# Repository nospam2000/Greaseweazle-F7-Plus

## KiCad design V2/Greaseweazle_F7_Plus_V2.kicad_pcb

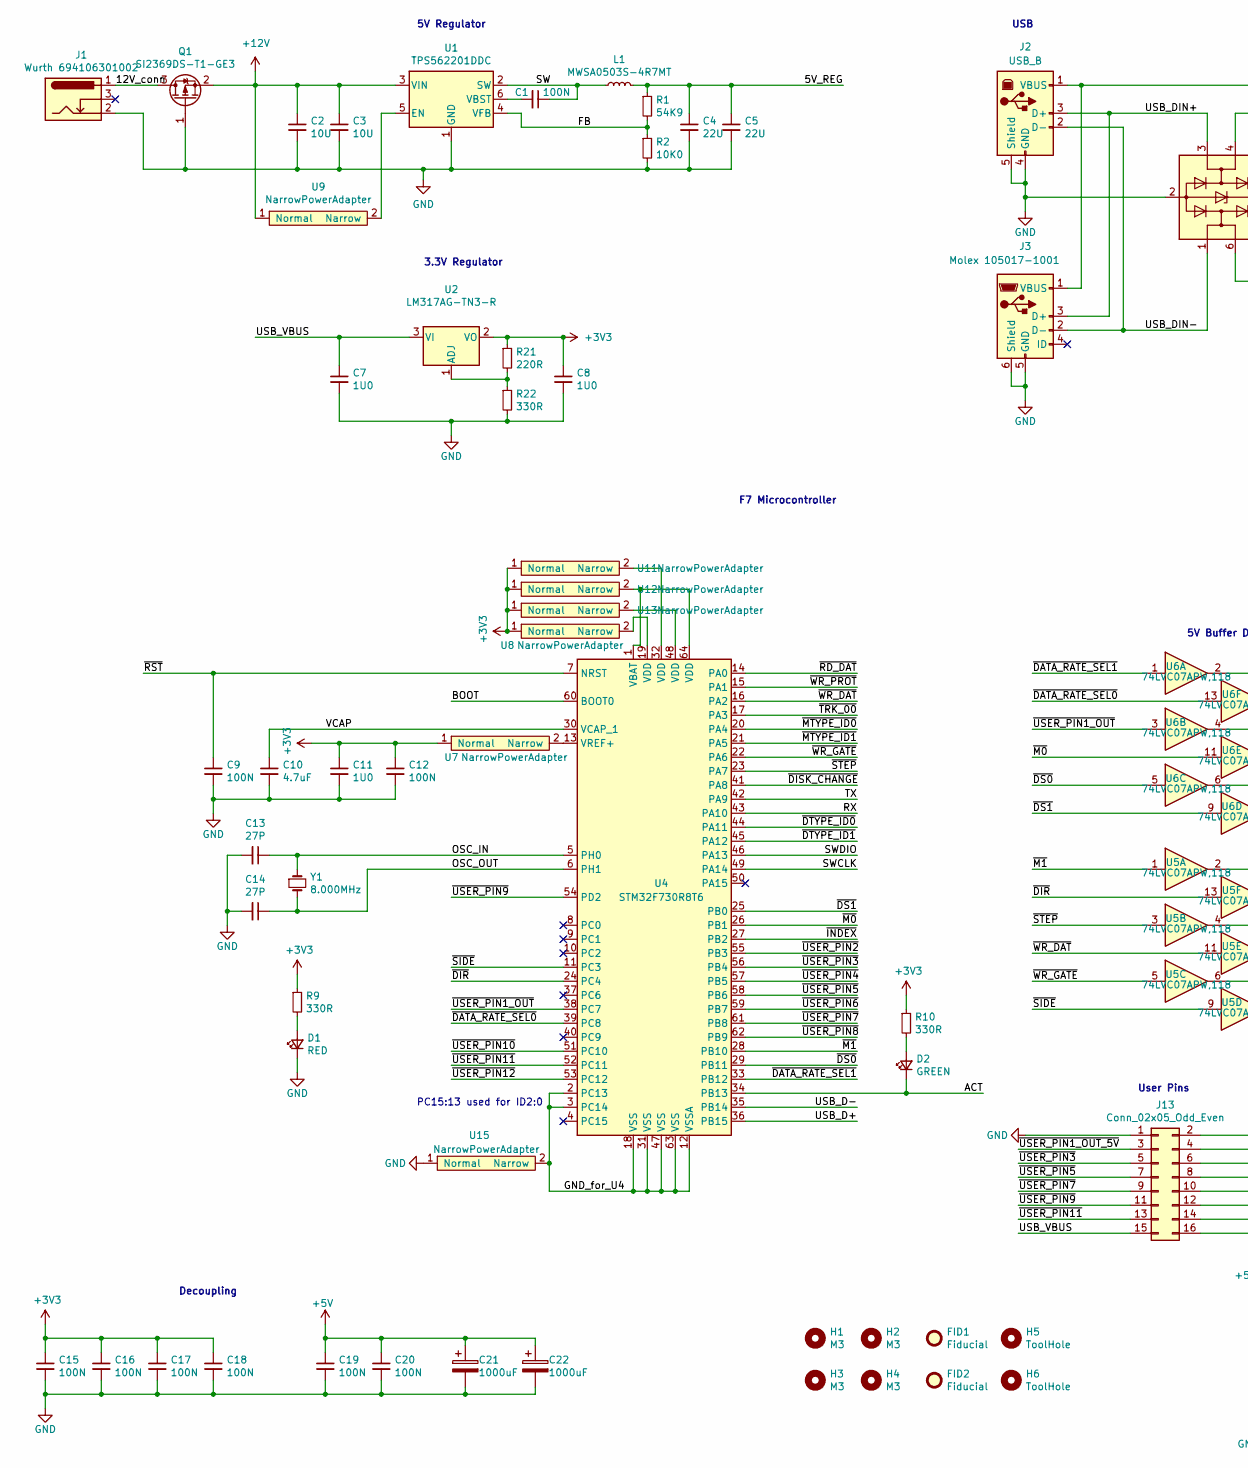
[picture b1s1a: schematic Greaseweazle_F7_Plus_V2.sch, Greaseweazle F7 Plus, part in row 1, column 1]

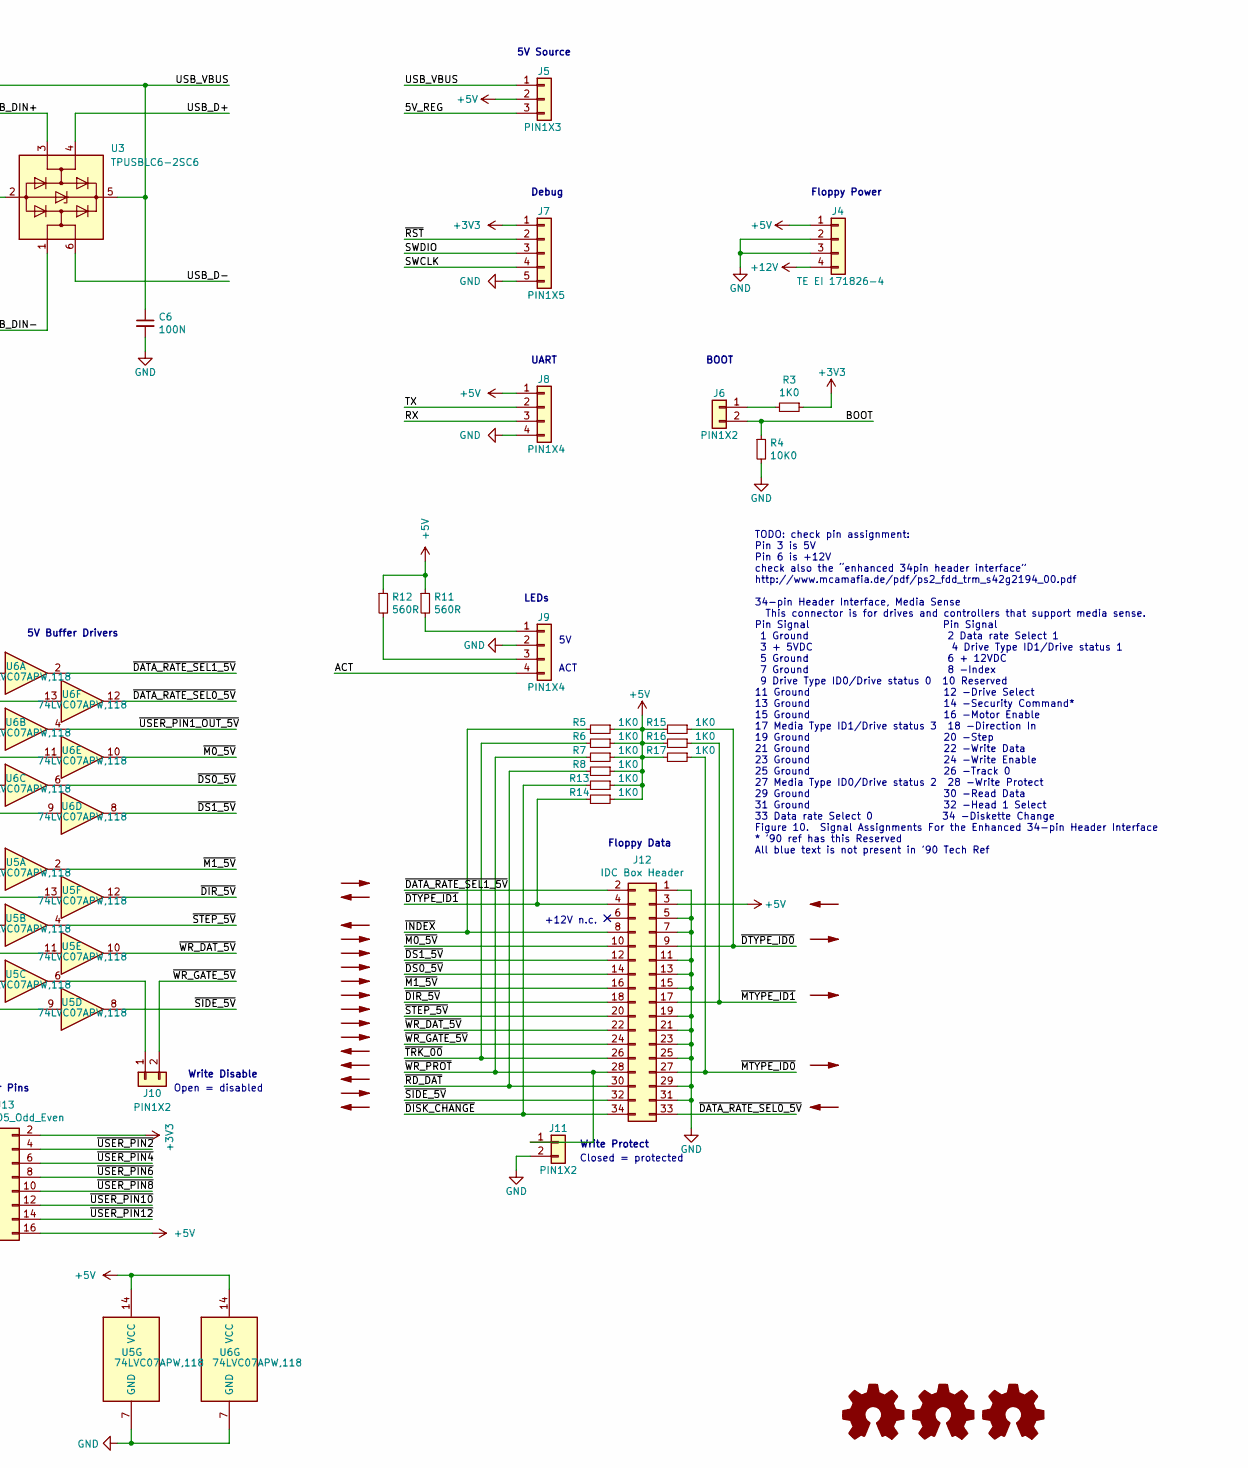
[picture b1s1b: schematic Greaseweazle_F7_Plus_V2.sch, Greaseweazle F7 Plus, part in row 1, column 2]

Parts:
C1, C6, C9, C12, C15, C16, C17, C18, C19, C20: 100N; C_0402_1005Metric; MFR.Part CL05B104KO5NNNC; LCSC C1525
C2, C3: 10U; C_0805_2012Metric; MFR.Part CL21A106KAYNNNE; LCSC C15850
C4, C5: 22U; C_0805_2012Metric; MFR.Part CL21A226MAQNNNE; LCSC C45783
C7, C8, C11: 1U0; C_0402_1005Metric; MFR.Part CL05A105KA5NQNC; LCSC C52923
C10: 4.7uF; C_0805_2012Metric; MFR.Part CL21A475KAQNNNE; LCSC C1779
C13, C14: 27P; C_0402_1005Metric; MFR.Part 0402CG270J500NTN; LCSC C1557
C21, C22: 1000uF; CP_Radial_D10.0mm_P5.00mm
D1: RED; LED_0603_1608Metric; MFR.Part KT-0603R; LCSC C2286
D2: GREEN; LED_0603_1608Metric; MFR.Part 19-217/GHC-YR1S2/3T; LCSC C72043
FID1, FID2: Fiducial; Fiducial_1mm_Mask2mm
H1, H2, H3, H4: M3; MountingHole_3mm
H5, H6: ToolHole; ToolingHole_1.152mm
J1: Wurth 694106301002; BarrelJack_Horizontal
J2: USB_B; USB_B_OST_USB-B1HSxx_Horizontal
J3: Molex 105017-1001; USB_Micro-B_Molex-105017-0001
J4: TE EI 171826-4; TE_171826-4_1x4_P2.50mm_Horizontal
J5: PIN1X3; PinHeader_1x03_P2.54mm_Vertical
J6, J10, J11: PIN1X2; PinHeader_1x02_P2.54mm_Vertical
J7: PIN1X5; PinHeader_1x05_P2.54mm_Vertical
J8, J9: PIN1X4; PinHeader_1x04_P2.54mm_Vertical
J12: IDC Box Header; IDC-Header_2x17_P2.54mm_Vertical
J13: Conn_02x05_Odd_Even; PinHeader_2x08_P2.54mm_Vertical
L1: MWSA0503S-4R7MT; L_5.4x5.2_H2.8; MFR.Part MWSA0503S-4R7MT; LCSC C408410
LOGO1: OSHW Logo; OSHW-Logo2_7.3x6mm_SilkScreen
LOGO2: GW Logo; Greaseweazle_Logo_small
LOGO3: GW Logo; Symbol_Barrel_Polarity
Q1: SI2369DS-T1-GE3; SOT-23; MFR.Part SI2369DS-T1-GE3; LCSC C141546
R1: 54K9; R_0603_1608Metric; MFR.Part 0603WAF5492T5E; LCSC C23077
R2, R4: 10K0; R_0603_1608Metric; MFR.Part 0603WAF1002T5E; LCSC C25804
R3, R5, R6, R7, R8, R13, R14, R15, R16, R17: 1K0; R_0805_2012Metric; MFR.Part 0805W8F1001T5E; LCSC C17513
R9, R10, R22: 330R; R_0805_2012Metric; MFR.Part 0805W8F3300T5E; LCSC C17630
R11, R12: 560R; R_0805_2012Metric; MFR.Part 0805W8F5600T5E; LCSC C28636
R21: 220R; R_0805_2012Metric; MFR.Part 0805W8F2200T5E; LCSC C17557
U1: TPS562201DDC; SOT-23-6; MFR.Part TPS562201DDCR; LCSC C90061
U2: LM317AG-TN3-R; TO-252-2; MFR.Part LM317AG-TN3-R; LCSC C75510
U3: TPUSBLC6-2SC6; SOT-23-6; MFR.Part TPUSBLC6-2SC6; LCSC C558442
U4: STM32F730R8T6; LQFP-64_10x10mm_P0.5mm; MFR.Part STM32F730R8T6; LCSC C478453
U5, U6: 74LVC07APW,118; TSSOP-14_4.4x5mm_P0.65mm; MFR.Part 74LVC07APW,118; LCSC C6051
U7, U8, U9, U11, U12, U13: NarrowPowerAdapter; NarrowPowerAdapter_0.60_to_0.25
U15: NarrowPowerAdapter; NarrowPowerAdapter_0.60_to_0.25_thick
Y1: 8.000MHz; Crystal_SMD_5032-2Pin_5.0x3.2mm; MFR.Part X50328MSB2GI; LCSC C115962

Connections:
+3V3: C8.1, C11.1, C12.1, C15.1, C16.1, C17.1, C18.1, J7.1, J13.2, R3.1, R9.1, R10.1, R21.1, U2.2 (VO), U7.1 (Normal), U8.1 (Normal), U11.1 (Normal), U12.1 (Normal), U13.1 (Normal)
+5V: C19.1, C20.1, C21.1, C22.1, J4.1, J5.2, J8.1, J12.3, J13.16, R5.1, R6.1, R7.1, R8.1, R11.1, R12.1, R13.1, R14.1, R15.2, R16.2, R17.2, U5.14 (VCC), U6.14 (VCC)
+12V: C2.1, C3.1, J4.4, Q1.2 (S), U1.3 (VIN), U9.1 (Normal)
/5V_REG: C4.1, C5.1, J5.3, L1.2, R1.1
/12V_conn: J1.1, Q1.3 (D)
/ACT: D2.1 (K), J9.4, U4.34 (PB13)
/BOOT: J6.2, R4.1, U4.60 (BOOT0)
/FB: R1.2, R2.1, U1.4 (VFB)
/GND_for_U4: U4.2 (PC13), U4.3 (PC14), U4.12 (VSSA), U4.18 (VSS), U4.31 (VSS), U4.47 (VSS), U4.63 (VSS), U15.2 (Narrow)
/OSC_IN: C13.1, U4.5 (PH0), Y1.1
/OSC_OUT: C14.1, U4.6 (PH1), Y1.2
/RX: J8.3, U4.43 (PA10)
/SW: C1.1, L1.1, U1.2 (SW)
/SWCLK: J7.4, U4.49 (PA14)
/SWDIO: J7.3, U4.46 (PA13)
/TX: J8.2, U4.42 (PA9)
/USB_D+: U3.4 (I/O2), U4.36 (PB15)
/USB_D-: U3.6 (I/O1), U4.35 (PB14)
/USB_DIN+: J2.3 (D+), J3.3 (D+), U3.3 (I/O2)
/USB_DIN-: J2.2 (D-), J3.2 (D-), U3.1 (I/O1)
/USB_VBUS: C6.1, C7.1, J2.1 (VBUS), J3.1 (VBUS), J5.1, J13.15, U2.3 (VI), U3.5 (VBUS)
/VCAP: C10.1, U4.30 (VCAP_1)
/~DATA_RATE_SEL0_5V~: J12.33, U6.12
/~DATA_RATE_SEL0~: U4.39 (PC8), U6.13
/~DATA_RATE_SEL1_5V~: J12.2, U6.2
/~DATA_RATE_SEL1~: U4.33 (PB12), U6.1
/~DIR_5V~: J12.18, U5.12
/~DIR~: U4.24 (PC4), U5.13
/~DISK_CHANGE~: J12.34, R13.2, U4.41 (PA8)
/~DS0_5V~: J12.14, U6.6
/~DS0~: U4.29 (PB11), U6.5
/~DS1_5V~: J12.12, U6.8
/~DS1~: U4.25 (PB0), U6.9
/~DTYPE_ID0~: J12.9, R15.1, U4.44 (PA11)
/~DTYPE_ID1~: J12.4, R14.2, U4.45 (PA12)
/~INDEX~: J12.8, R5.2, U4.27 (PB2)
/~M0_5V~: J12.10, U6.10
/~M0~: U4.26 (PB1), U6.11
/~M1_5V~: J12.16, U5.2
/~M1~: U4.28 (PB10), U5.1
/~MTYPE_ID0~: J12.27, R17.1, U4.20 (PA4)
/~MTYPE_ID1~: J12.17, R16.1, U4.21 (PA5)
/~RD_DAT~: J12.30, R8.2, U4.14 (PA0)
/~RST~: C9.1, J7.2, U4.7 (NRST)
/~SIDE_5V~: J12.32, U5.8
/~SIDE~: U4.11 (PC3), U5.9
/~STEP_5V~: J12.20, U5.4
/~STEP~: U4.23 (PA7), U5.3
/~TRK_00~: J12.26, R6.2, U4.17 (PA3)
/~USER_PIN1_OUT_5V~: J13.3, U6.4
/~USER_PIN1_OUT~: U4.38 (PC7), U6.3
/~USER_PIN2~: J13.4, U4.55 (PB3)
/~USER_PIN3~: J13.5, U4.56 (PB4)
/~USER_PIN4~: J13.6, U4.57 (PB5)
/~USER_PIN5~: J13.7, U4.58 (PB6)
/~USER_PIN6~: J13.8, U4.59 (PB7)
/~USER_PIN7~: J13.9, U4.61 (PB8)
/~USER_PIN8~: J13.10, U4.62 (PB9)
/~USER_PIN9~: J13.11, U4.54 (PD2)
/~USER_PIN10~: J13.12, U4.51 (PC10)
/~USER_PIN11~: J13.13, U4.52 (PC11)
/~USER_PIN12~: J13.14, U4.53 (PC12)
/~WR_DAT_5V~: J12.22, U5.10
/~WR_DAT~: U4.16 (PA2), U5.11
/~WR_GATE_5V~: J10.2, J12.24
/~WR_GATE~: U4.22 (PA6), U5.5
/~WR_PROT~: J11.1, J12.28, R7.2, U4.15 (PA1)
GND: C2.2, C3.2, C4.2, C5.2, C6.2, C7.2, C8.2, C9.2, C10.2, C11.2, C12.2, C13.2, C14.2, C15.2, C16.2, C17.2, C18.2, C19.2, C20.2, C21.2, C22.2, D1.1 (K), J1.2, J2.4 (GND), J2.5 (Shield), J3.5 (GND), J3.6 (Shield), J4.2, J4.3, J7.5, J8.4, J9.2, J11.2, J12.1, J12.5, J12.7, J12.11, J12.13, J12.15, J12.19, J12.21, J12.23, J12.25, J12.29, J12.31, J13.1, Q1.1 (G), R2.2, R4.2, R22.2, U1.1 (GND), U3.2 (GND), U5.7 (GND), U6.7 (GND), U15.1 (Normal)
unnamed: C1.2, U1.6 (VBST)
unnamed: D1.2 (A), R9.2
unnamed: D2.2 (A), R10.2
unnamed: J6.1, R3.2
unnamed: J9.1, R11.2
unnamed: J9.3, R12.2
unnamed: J10.1, U5.6
unnamed: R21.2, R22.1, U2.1 (ADJ)
unnamed: U1.5 (EN), U9.2 (Narrow)
unnamed: U4.13 (VREF+), U7.2 (Narrow)
unnamed: U4.19 (VDD), U8.2 (Narrow)
unnamed: U4.32 (VDD), U11.2 (Narrow)
unnamed: U4.1 (VBAT), U4.64 (VDD), U12.2 (Narrow)
unnamed: U4.48 (VDD), U13.2 (Narrow)

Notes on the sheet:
UART
Debug
Floppy Power
BOOT
USB
Floppy Data
5V Regulator
5V Buffer Drivers
3.3V Regulator
5V Source
F7 Microcontroller
Decoupling
LEDs
PC15:13 used for ID2:0
ACT
Write Protect
Write Disable
Open = disabled
Closed = protected
TODO: check pin assignment: Pin 3 is 5V Pin 6 is +12V check also the “enhanced 34pin header interface” http://www.mcamafia.de/pdf/ps2_fdd_trm_s42g2194_00.pdf 34-pin Header Interface, Media Sense This connector is for drives and controllers that support media sense. Pin Signal Pin Signal 1 Ground 2 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
+12V n.c.
User Pins

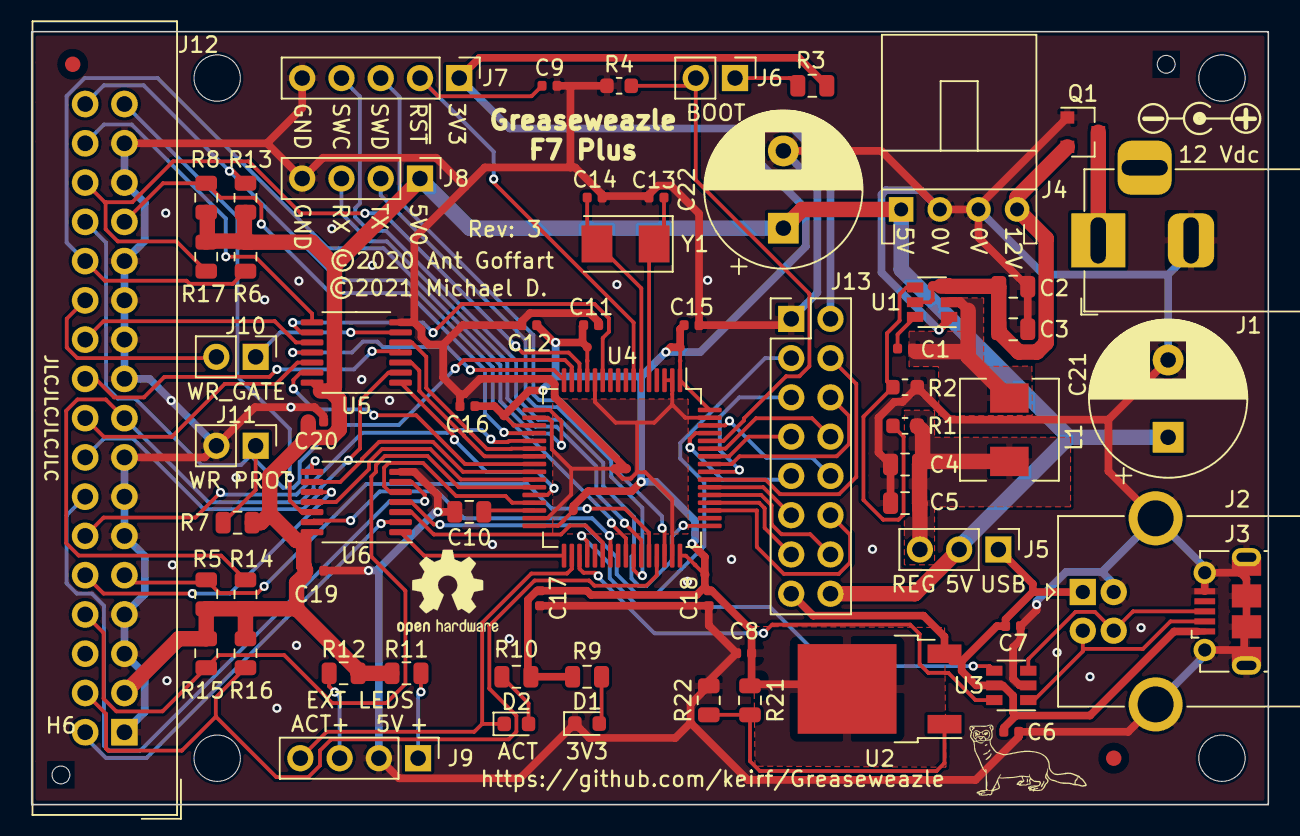
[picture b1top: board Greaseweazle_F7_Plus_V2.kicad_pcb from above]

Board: 2 copper layers, 80.0 x 50.0 mm, 83 parts (0 on the bottom side), 82 nets.

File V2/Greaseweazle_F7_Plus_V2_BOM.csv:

Comment,Designator,Footprint,LCSC
"4.7uF","C10","Capacitor_SMD:C_0805_2012Metric","C1779"
"27P","C13,C14","Capacitor_SMD:C_0402_1005Metric","C1557"
"100N","C1,C6,C9,C12,C15,C16,C17,C18,C19,C20","Capacitor_SMD:C_0402_1005Metric","C1525"
"10U","C2,C3","Capacitor_SMD:C_0805_2012Metric","C15850"
"1000uF","C21,C22","Capacitor_THT:CP_Radial_D10.0mm_P5.00mm",""
"22U","C4,C5","Capacitor_SMD:C_0805_2012Metric","C45783"
"1U0","C7,C8,C11","Capacitor_SMD:C_0402_1005Metric","C52923"
"RED","D1","LED_SMD:LED_0603_1608Metric","C2286"
"GREEN","D2","LED_SMD:LED_0603_1608Metric","C72043"
"Fiducial","FID1,FID2","Fiducial:Fiducial_1mm_Mask2mm",""
"M3","H1,H2,H3,H4","MountingHole:MountingHole_3mm",""
"ToolHole","H5,H6","greaseweazle:ToolingHole_1.152mm",""
"Wurth 694106301002","J1","Connector_BarrelJack:BarrelJack_Horizontal",""
"IDC Box Header","J12","Connector_IDC:IDC-Header_2x17_P2.54mm_Vertical",""
"Conn_02x05_Odd_Even","J13","Connector_PinHeader_2.54mm:PinHeader_2x08_P2.54mm_Vertical",""
"USB_B","J2","Connector_USB:USB_B_OST_USB-B1HSxx_Horizontal",""
"Molex 105017-1001","J3","Connector_USB:USB_Micro-B_Molex-105017-0001",""
"TE EI 171826-4","J4","AmberTronic:TE_171826-4_1x4_P2.50mm_Horizontal",""
"PIN1X3","J5","Connector_PinHeader_2.54mm:PinHeader_1x03_P2.54mm_Vertical",""
"PIN1X2","J6,J10,J11","Connector_PinHeader_2.54mm:PinHeader_1x02_P2.54mm_Vertical",""
"PIN1X5","J7","Connector_PinHeader_2.54mm:PinHeader_1x05_P2.54mm_Vertical",""
"PIN1X4","J8,J9","Connector_PinHeader_2.54mm:PinHeader_1x04_P2.54mm_Vertical",""
"MWSA0503S-4R7MT","L1","greaseweazle:L_5.4x5.2_H2.8","C408410"
"OSHW Logo","LOGO1","Symbol:OSHW-Logo2_7.3x6mm_SilkScreen",""
"GW Logo","LOGO2","greaseweazle:Greaseweazle_Logo_small",""
"GW Logo","LOGO3","Symbol:Symbol_Barrel_Polarity",""
"SI2369DS-T1-GE3","Q1","Package_TO_SOT_SMD:SOT-23","C141546"
"54K9","R1","Resistor_SMD:R_0603_1608Metric","C23077"
"560R","R11,R12","Resistor_SMD:R_0805_2012Metric","C28636"
"220R","R21","Resistor_SMD:R_0805_2012Metric","C17557"
"1K0","R3,R5,R6,R7,R8,R13,R14,R15,R16,R17","Resistor_SMD:R_0805_2012Metric","C17513"
"10K0","R2,R4","Resistor_SMD:R_0603_1608Metric","C25804"
"330R","R9,R10,R22","Resistor_SMD:R_0805_2012Metric","C17630"
"TPS562201DDC","U1","Package_TO_SOT_SMD:SOT-23-6","C90061"
"NarrowPowerAdapter","U15","greaseweazle:NarrowPowerAdapter_0.60_to_0.25_thick",""
"LM317AG-TN3-R","U2","Package_TO_SOT_SMD:TO-252-2","C75510"
"TPUSBLC6-2SC6","U3","Package_TO_SOT_SMD:SOT-23-6","C558442"
"STM32F730R8T6","U4","Package_QFP:LQFP-64_10x10mm_P0.5mm","C478453"
"74LVC07APW,118","U5,U6","Package_SO:TSSOP-14_4.4x5mm_P0.65mm","C6051"
"NarrowPowerAdapter","U7,U8,U9,U11,U12,U13","greaseweazle:NarrowPowerAdapter_0.60_to_0.25",""
"8.000MHz","Y1","Crystal:Crystal_SMD_5032-2Pin_5.0x3.2mm","C115962"

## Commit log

2021-01-06 added JLCPBC component ids, adapted footprints changed components which are no available in JLCPCB catalog
2021-01-07 made autorouting possible use components which are in stock on JLCPCB
2021-01-07 fixed rotation of U3
2021-01-08 fixed copper fill zones
2021-01-08 decreased keep out area around tooling holes
2021-01-08 changed copper zone pad connection of L1 to "thermal reliefs"
2021-01-08 added copper fill below mcu and L1 improved power connections of mcu
2021-01-08 added via to get better copper fill made 5Vreg thicker
2021-01-08 updated production output files
2021-01-09 changed C10 from 10u to 4.7u according to STM doc changed 74LS07 to 74LVC07APW,118 to reduce cost
2021-01-09 routed latest version
2021-01-09 production files for latest version
2021-01-09 replaced 3.3V regulator by cheaper one moved many parts to make space
2021-01-09 added 2nd CMT file to remove 5V regulator to save cost rotated U2 back by 180° added vias to get better copperfill
2021-01-09 added 3x 10000uF caps to buffer motor start of floppy which can draw up to 1A
2021-01-09 fixed copyright and greaseweazel silk
2021-01-09 added greaseweazel logo to library
2021-01-09 moved U11 NarrowPowCon to get better routing
2021-01-10 fixed footprint+silk of polarized caps
2021-01-10 thicker connection for copper pours
2021-01-10 added silk for powerconn polarity
2021-01-10 use enhanced floppy interface
    use this document as reference: http://www.mcamafia.de/pdf/ps2_fdd_trm_s42g2194_00.pdf
    IBM Personal System/2
    3.5inch Diskette drives
    Technical Reference 42G2194 S42G-2194-00
    This version is no longer compatible to original firmware because
    some connections changed
2021-01-10 moved components to optimize routing
2021-01-10 optimized silk of R's on the left side
2021-01-10 updated production files
2021-01-10 added changed pin definitions
2021-01-10 ignore unneeded files
2021-01-13 added user pin connector removed C23
2021-01-13 moved user pin conn and voltage reg to make more space for the casing of the user pin conn

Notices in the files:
V2/Greaseweazle_F7_Plus_V2.kicad_pcb:
©2021 Michael D.
©2020 Ant Goffart
